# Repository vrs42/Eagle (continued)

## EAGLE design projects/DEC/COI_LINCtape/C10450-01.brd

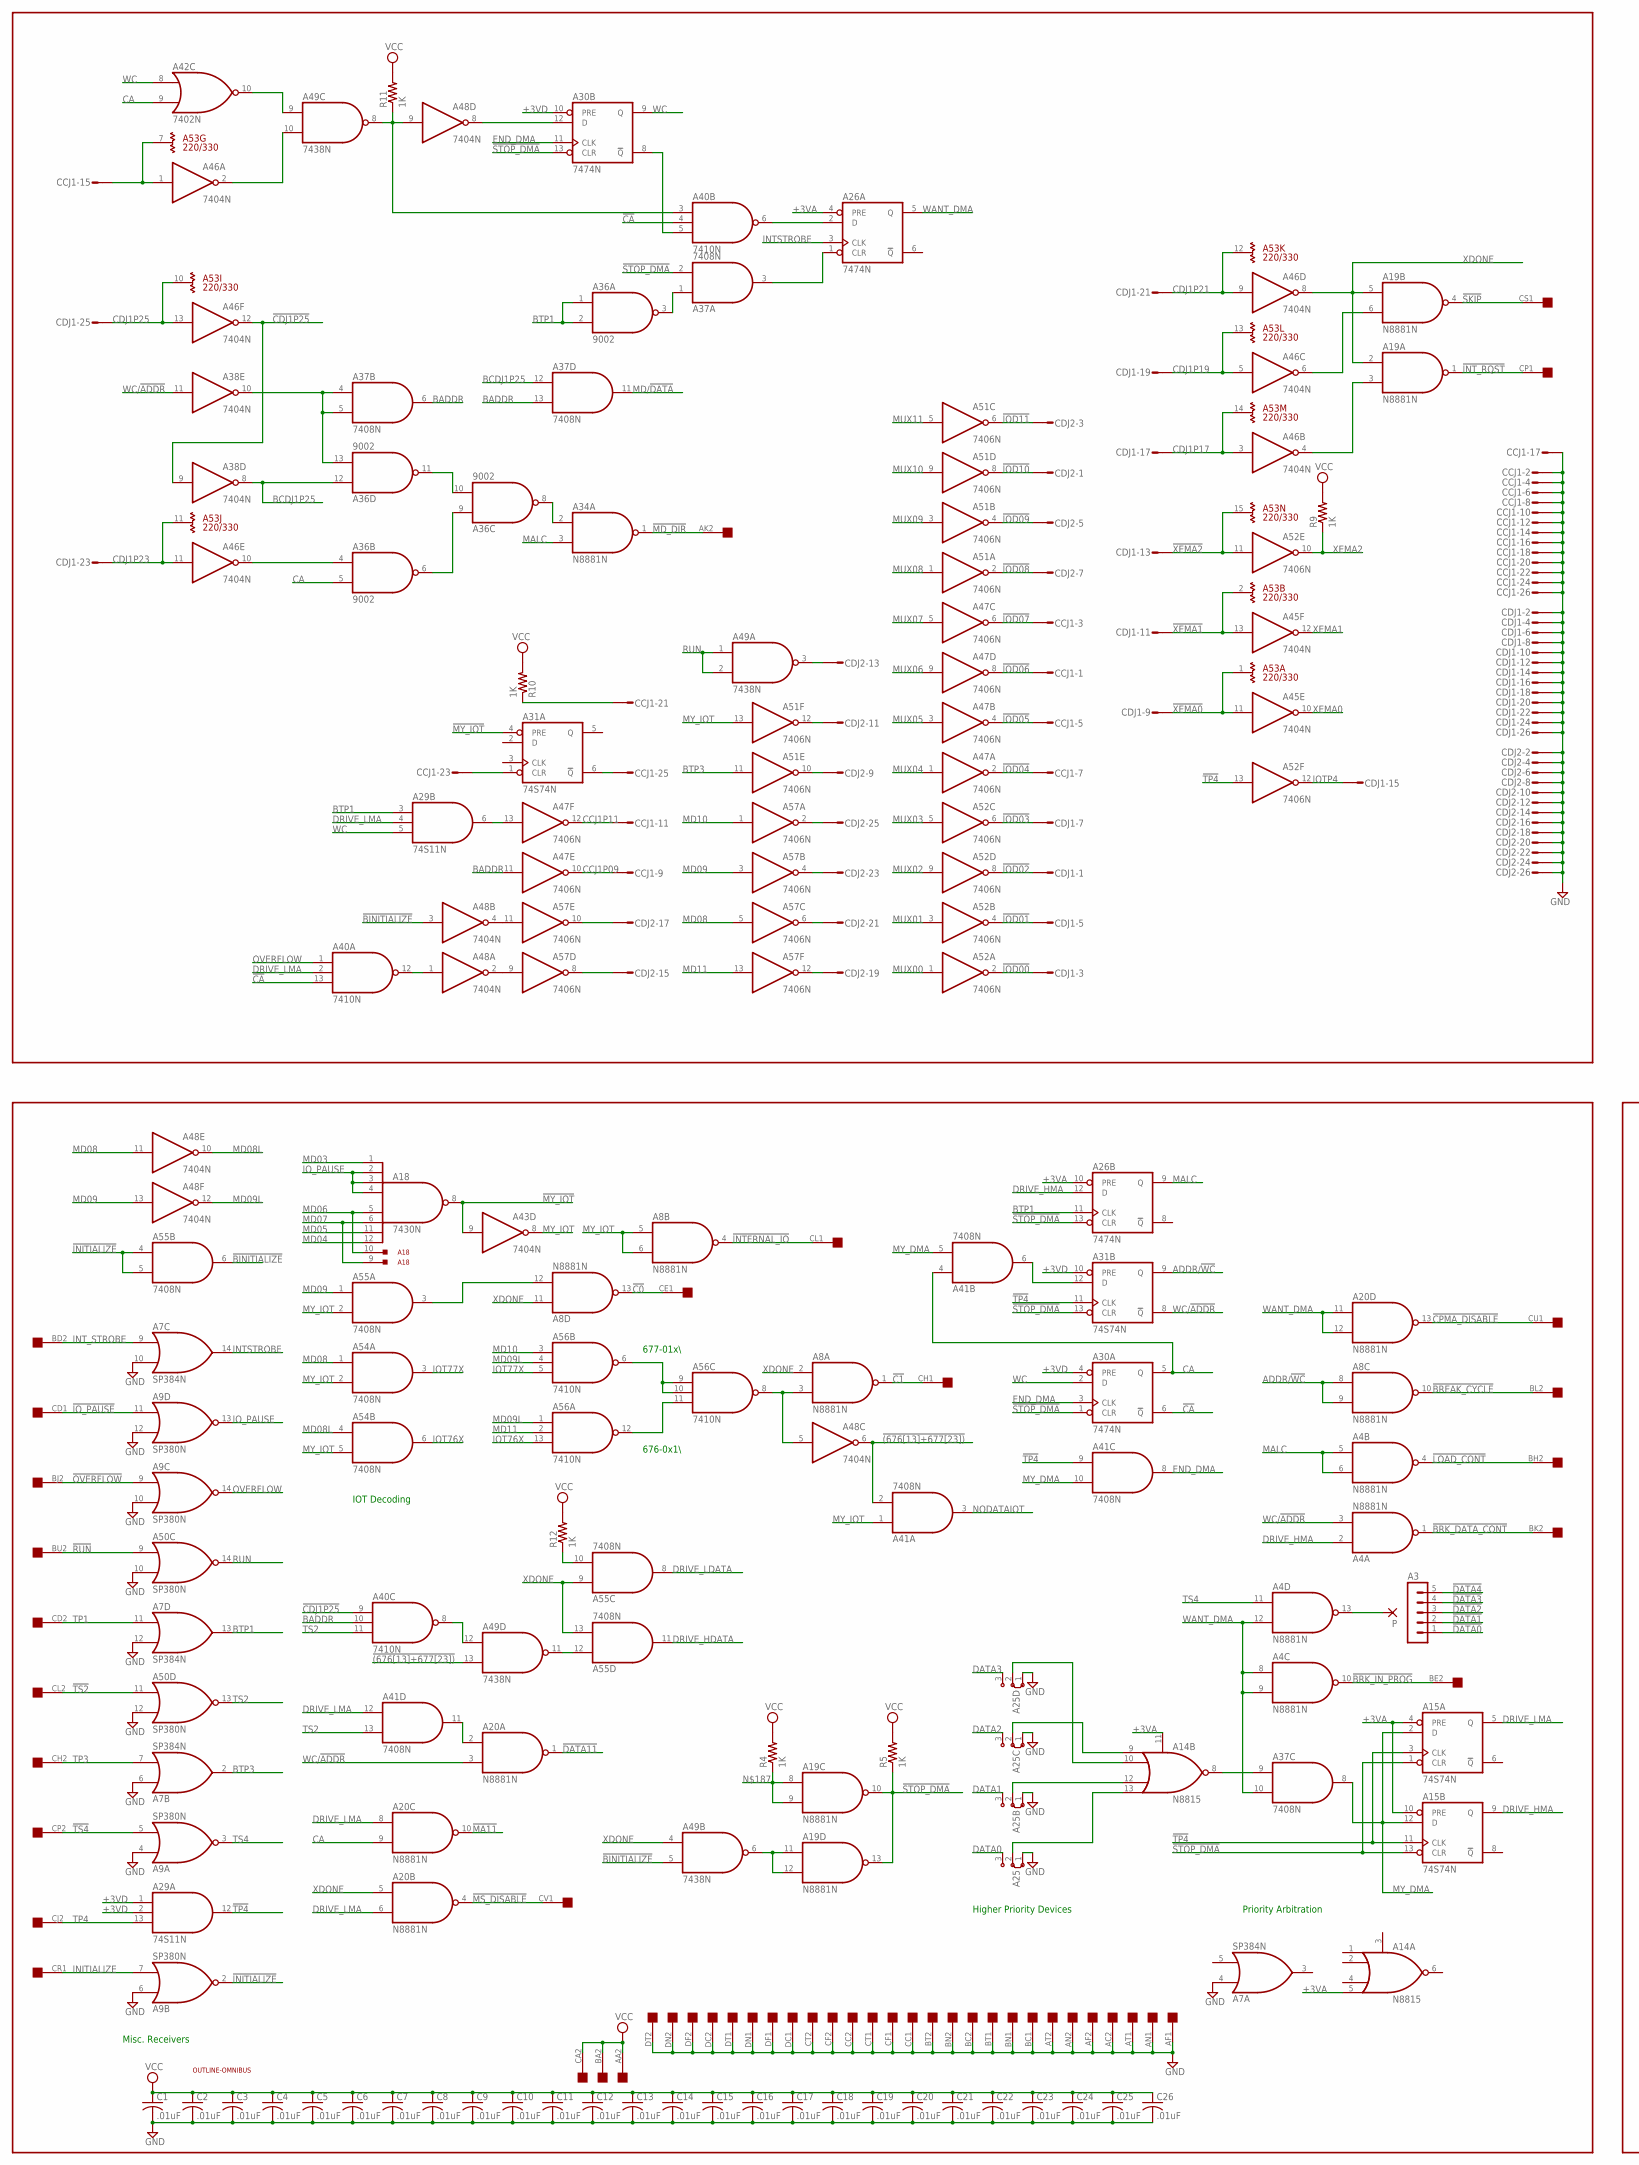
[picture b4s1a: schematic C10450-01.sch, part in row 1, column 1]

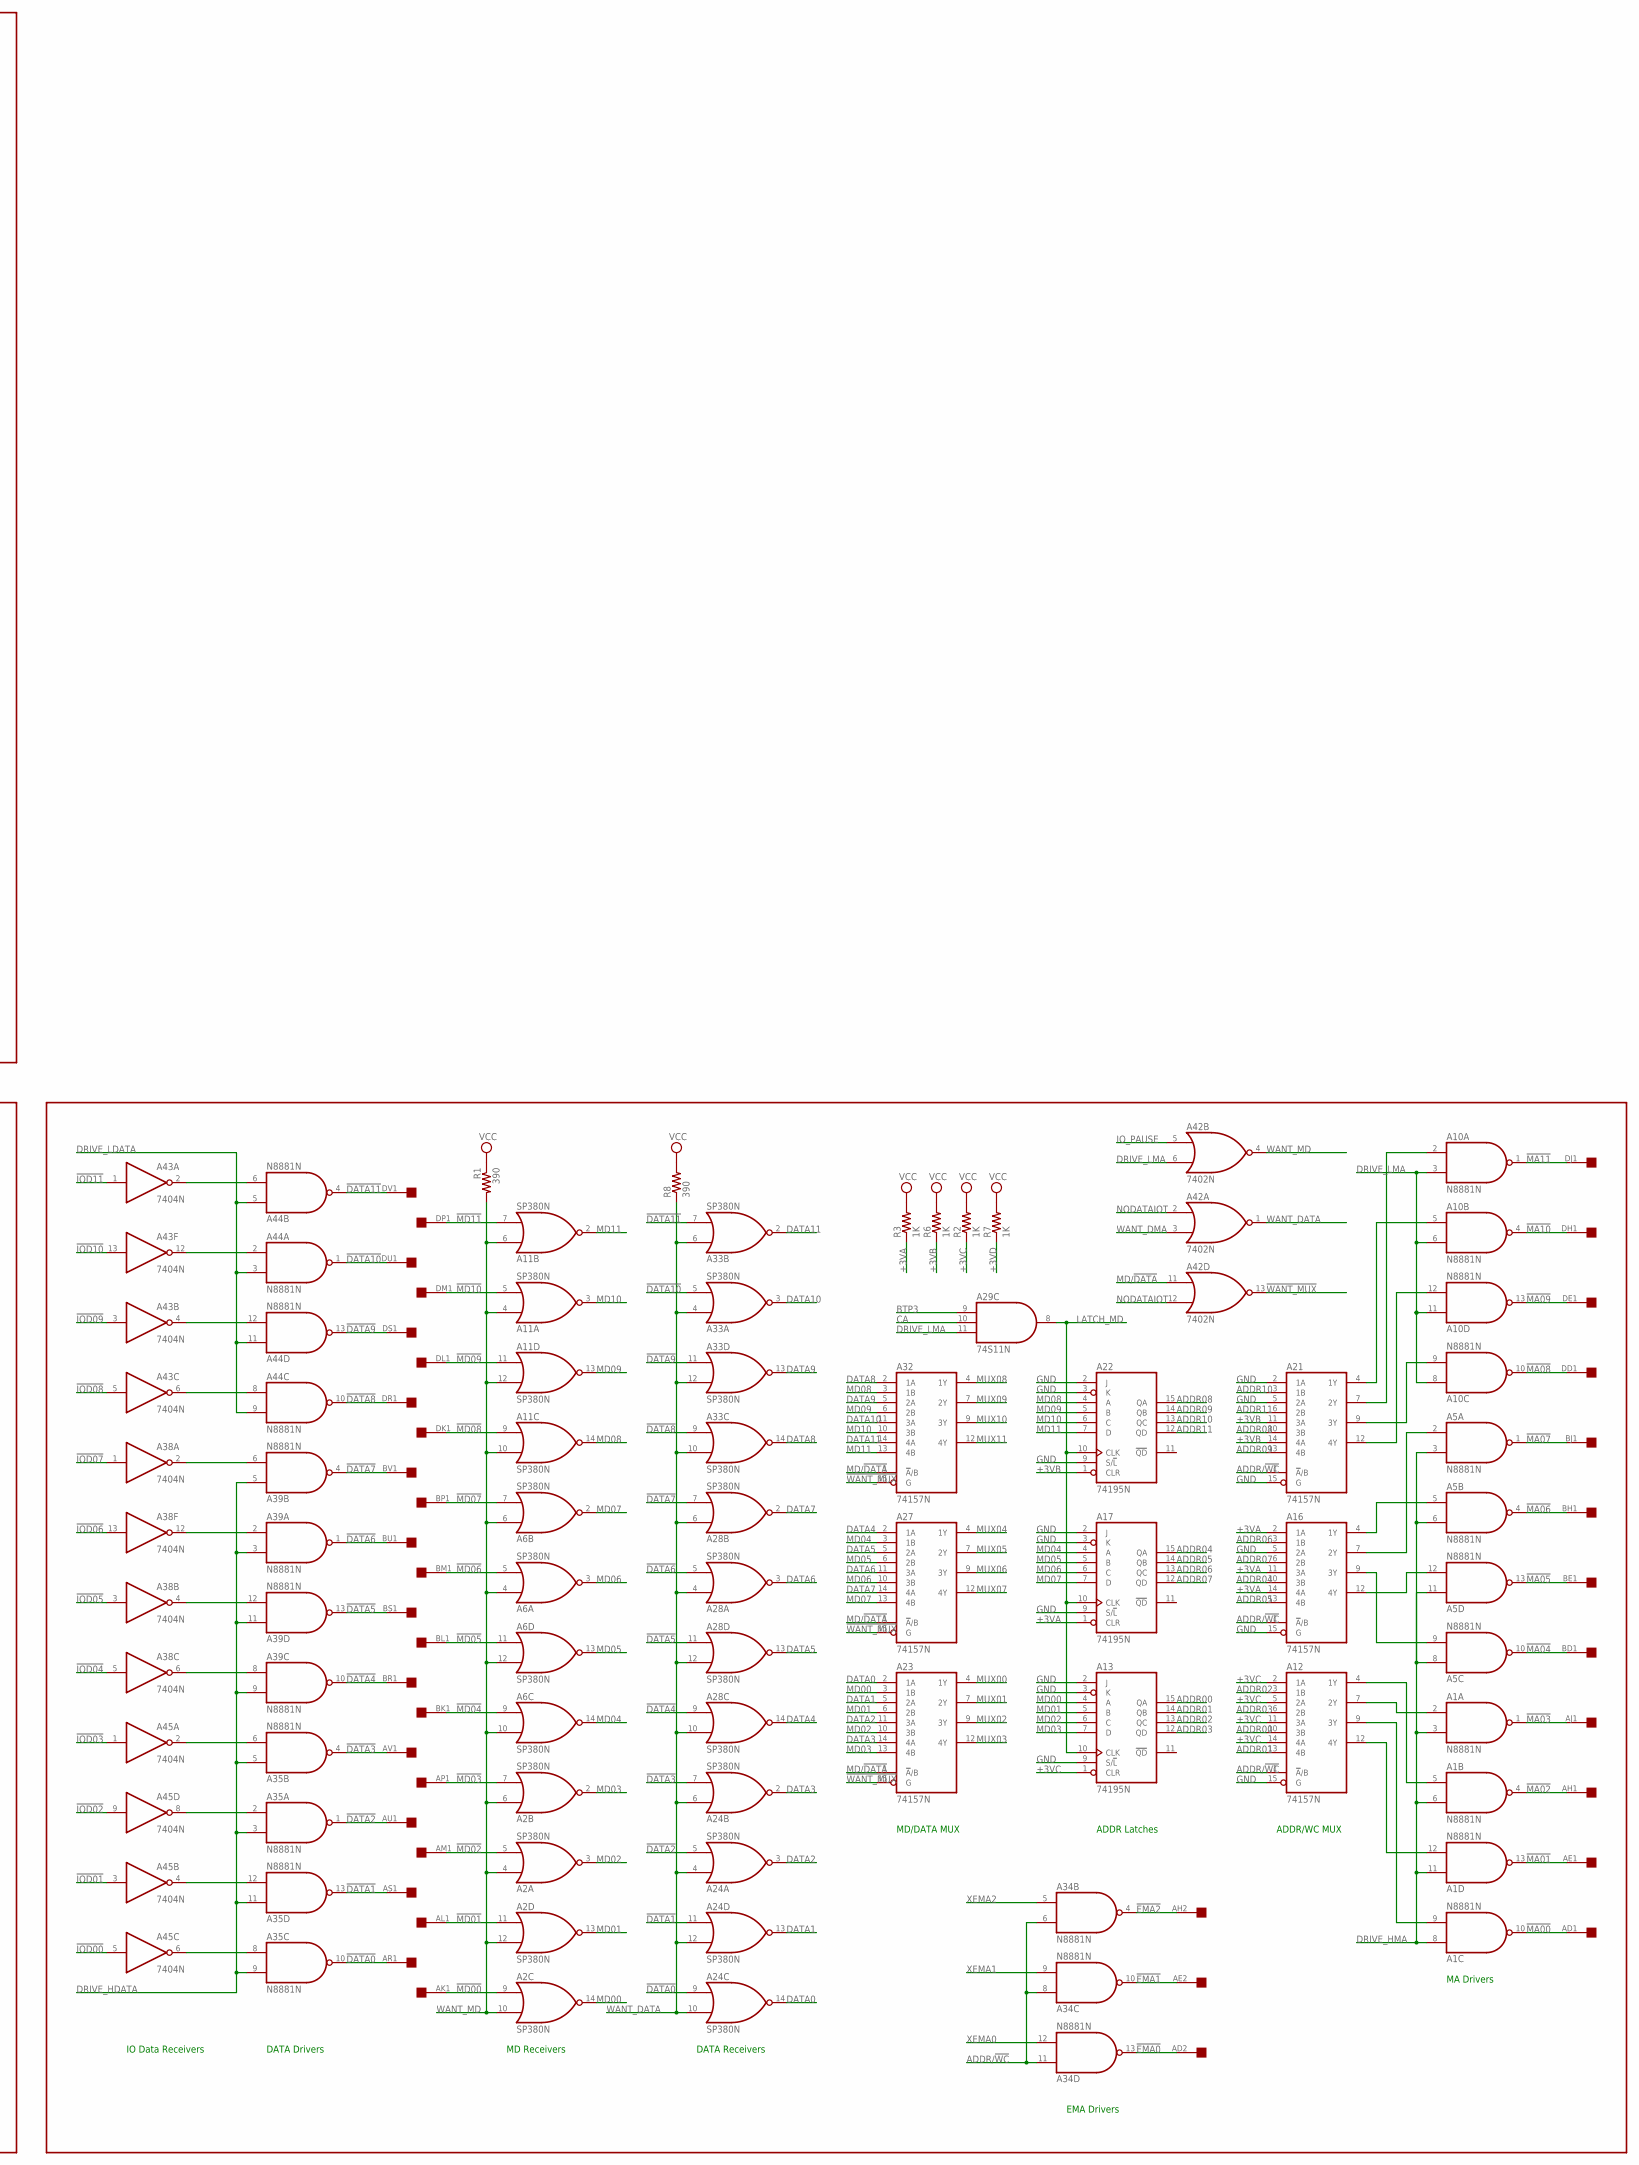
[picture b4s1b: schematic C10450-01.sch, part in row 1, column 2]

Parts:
A1, A4, A5, A8, A10, A19, A20, A34, A35, A39, A44: N8881N; DIL14
A2, A6, A9, A11, A24, A28, A33, A50: SP380N; DIL14
A3: MA05-1
A7: SP384N; DIL14
A12, A16, A21, A23, A27, A32: 74157N; DIL16
A13, A17, A22: 74195N; DIL16
A14: N8815; DIL14
A15, A31: 74S74N; DIL14
A18: 7430N; DIL14
A25, A25B, A25C, A25D: J2X5MM; 05C
A26, A30: 7474N; DIL14
A29: 74S11N; DIL14
A36: 9002; DIL14
A37, A41, A54, A55: 7408N; DIL14
A38, A43, A45, A46, A48: 7404N; DIL14
A40, A56: 7410N; DIL14
A42: 7402N; DIL14
A47, A51, A52, A57: 7406N; DIL14
A49: 7438N; DIL14
A53: 220/330; DIL16
C1, C2, C3, C4, C5, C6, C7, C8, C9, C10, C11, C12, C13, C14, C15, C16, C17, C18, C19, C20, C21, C22, C23, C24, C25, C26: .01uF; C050-025X075
CCJ1: 26HS; 26H
CDJ1, CDJ2: 26HS; 26H
P: 1,6/0,8
R1, R8: 390; 0207/10
R2, R3, R4, R5, R6, R7, R9, R10, R11, R12: 1K; 0207/10
U$1: OUTLINE-OMNIBUS; OMNIBUS
U$2: QUAD; EDGE-CON8

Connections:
!(676[13]+677[23]): A41.2 (I1), A48.6 (O), A49.13 (I1)
!BINITIALIZE: A48.3 (I), A49.5 (I1), A55.6 (O)
!BREAK_CYCLE: A8.10 (O), U$2.BL2
!BRK_DATA_CONT: A4.1 (O), U$2.BK2
!BRK_IN_PROG: A4.10 (O), U$2.BE2
!C0: A8.13 (O), U$2.CE1
!C1: A8.1 (O), U$2.CH1
!CA: A30.6 (!Q), A40.4 (I1), A40.13 (I2)
!CDJ1P25: A38.9 (I), A40.9 (I0), A46.12 (O)
!CPMA_DISABLE: A20.13 (O), U$2.CU1
!DATA0: A3.1, A24.9 (I0), A35.10 (O), U$2.AR1
!DATA1: A3.2, A24.11 (I0), A35.13 (O), U$2.AS1
!DATA2: A3.3, A24.5 (I1), A35.1 (O), U$2.AU1
!DATA3: A3.4, A24.7 (I1), A35.4 (O), U$2.AV1
!DATA4: A3.5, A28.9 (I0), A39.10 (O), U$2.BR1
!DATA5: A28.11 (I0), A39.13 (O), U$2.BS1
!DATA6: A28.5 (I1), A39.1 (O), U$2.BU1
!DATA7: A28.7 (I1), A39.4 (O), U$2.BV1
!DATA8: A33.9 (I0), A44.10 (O), U$2.DR1
!DATA9: A33.11 (I0), A44.13 (O), U$2.DS1
!DATA10: A33.5 (I1), A44.1 (O), U$2.DU1
!DATA11: A20.1 (O), A33.7 (I1), A44.4 (O), U$2.DV1
!EMA0: A34.13 (O), U$2.AD2
!EMA1: A34.10 (O), U$2.AE2
!EMA2: A34.4 (O), U$2.AH2
!INITIALIZE: A9.2 (O), A55.4 (I0), A55.5 (I1)
!INTERNAL_IO: A8.4 (O), U$2.CL1
!INT_RQST: A19.1 (O), U$2.CP1
!IOD00: A45.5 (I), A52.2 (O), CDJ1.3
!IOD01: A45.3 (I), A52.4 (O), CDJ1.5
!IOD02: A45.9 (I), A52.8 (O), CDJ1.1
!IOD03: A45.1 (I), A52.6 (O), CDJ1.7
!IOD04: A38.5 (I), A47.2 (O), CCJ1.7
!IOD05: A38.3 (I), A47.4 (O), CCJ1.5
!IOD06: A38.13 (I), A47.8 (O), CCJ1.1
!IOD07: A38.1 (I), A47.6 (O), CCJ1.3
!IOD08: A43.5 (I), A51.2 (O), CDJ2.7
!IOD09: A43.3 (I), A51.4 (O), CDJ2.5
!IOD10: A43.13 (I), A51.8 (O), CDJ2.1
!IOD11: A43.1 (I), A51.6 (O), CDJ2.3
!IO_PAUSE: A9.11 (I0), U$2.CD1
!LOAD_CONT: A4.4 (O), U$2.BH2
!MA00: A1.10 (O), U$2.AD1
!MA01: A1.13 (O), U$2.AE1
!MA02: A1.4 (O), U$2.AH1
!MA03: A1.1 (O), U$2.AJ1
!MA04: A5.10 (O), U$2.BD1
!MA05: A5.13 (O), U$2.BE1
!MA06: A5.4 (O), U$2.BH1
!MA07: A5.1 (O), U$2.BJ1
!MA08: A10.10 (O), U$2.DD1
!MA09: A10.13 (O), U$2.DE1
!MA10: A10.4 (O), U$2.DH1
!MA11: A10.1 (O), A20.10 (O), U$2.DJ1
!MD00: A2.9 (I0), U$2.AK1
!MD01: A2.11 (I0), U$2.AL1
!MD02: A2.5 (I1), U$2.AM1
!MD03: A2.7 (I1), U$2.AP1
!MD04: A6.9 (I0), U$2.BK1
!MD05: A6.11 (I0), U$2.BL1
!MD06: A6.5 (I1), U$2.BM1
!MD07: A6.7 (I1), U$2.BP1
!MD08: A11.9 (I0), U$2.DK1
!MD09: A11.11 (I0), U$2.DL1
!MD10: A11.5 (I1), U$2.DM1
!MD11: A11.7 (I1), U$2.DP1
!MD_DIR: A34.1 (O), U$2.AK2
!MS_DISABLE: A20.4 (O), U$2.CV1
!MY_IOT: A18.8 (O), A31.4 (PRE), A43.9 (I)
!OVERFLOW: A9.9 (I0), U$2.BJ2
!RUN: A50.9 (I0), U$2.BU2
!SKIP: A19.4 (O), U$2.CS1
!STOP_DMA: A15.1 (CLR), A15.13 (CLR), A19.10 (O), A19.13 (O), A26.13 (CLR), A30.1 (CLR), A30.13 (CLR), A31.13 (CLR), A37.2 (I1), R5.1
!TP4: A15.3 (CLK), A15.11 (CLK), A29.12 (O), A31.11 (CLK), A41.9 (I0), A52.13 (I)
!TS2: A50.11 (I0), U$2.CL2
!TS4: A9.5 (I1), U$2.CP2
!WANT_MUX: A23.15 (G), A27.15 (G), A32.15 (G), A42.13 (O)
!WC: A30.8 (!Q), A40.5 (I2)
!XEMA0: A45.11 (I), A53.1 (TERM), CDJ1.9
!XEMA1: A45.13 (I), A53.2 (TERM), CDJ1.11
!XEMA2: A52.11 (I), A53.15 (TERM), CDJ1.13
+3VA: A14.5 (I3), A14.11 (G), A15.4 (PRE), A15.10 (PRE), A16.2 (1A), A16.11 (3A), A16.14 (4A), A17.1 (CLR), A26.4 (PRE), A26.10 (PRE), R3.1
+3VB: A21.11 (3A), A21.14 (4A), A22.1 (CLR), R6.1
+3VC: A12.2 (1A), A12.5 (2A), A12.11 (3A), A12.14 (4A), A13.1 (CLR), R2.1
+3VD: A29.1 (I0), A29.2 (I1), A30.4 (PRE), A30.10 (PRE), A31.10 (PRE), R7.1
ADDR00: A12.10 (3B), A13.15 (QA)
ADDR01: A12.13 (4B), A13.14 (QB)
ADDR02: A12.3 (1B), A13.13 (QC)
ADDR03: A12.6 (2B), A13.12 (QD)
ADDR04: A16.10 (3B), A17.15 (QA)
ADDR05: A16.13 (4B), A17.14 (QB)
ADDR06: A16.3 (1B), A17.13 (QC)
ADDR07: A16.6 (2B), A17.12 (QD)
ADDR08: A21.10 (3B), A22.15 (QA)
ADDR09: A21.13 (4B), A22.14 (QB)
ADDR10: A21.3 (1B), A22.13 (QC)
ADDR11: A21.6 (2B), A22.12 (QD)
ADDR/!WC: A8.8 (I0), A8.9 (I1), A12.1 (!A!/B), A16.1 (!A!/B), A21.1 (!A!/B), A31.9 (Q), A34.6 (I1), A34.8 (I0), A34.11 (I0)
BADDR: A37.6 (O), A37.13 (I1), A40.10 (I1), A47.11 (I)
BCDJ1P25: A36.12 (I0), A37.12 (I0), A38.8 (O)
BTP1: A7.13 (O), A26.11 (CLK), A29.3 (I0), A36.1 (I0), A36.2 (I1)
BTP3: A7.2 (O), A29.9 (I0), A51.11 (I)
CA: A20.9 (I1), A29.10 (I1), A30.5 (Q), A36.5 (I1), A41.4 (I0), A42.9 (I1)
CCJ1P09: A47.10 (O), CCJ1.9
CCJ1P11: A47.12 (O), CCJ1.11
CDJ1P17: A46.3 (I), A53.14 (TERM), CDJ1.17
CDJ1P19: A46.5 (I), A53.13 (TERM), CDJ1.19
CDJ1P21: A46.9 (I), A53.12 (TERM), CDJ1.21
CDJ1P23: A46.11 (I), A53.11 (TERM), CDJ1.23
CDJ1P25: A46.13 (I), A53.10 (TERM), CDJ1.25
CDJ2P09: A51.10 (O), CDJ2.9
CDJ2P11: A51.12 (O), CDJ2.11
CDJ2P13: A49.3 (O), CDJ2.13
CDJ2P15: A57.8 (O), CDJ2.15
CDJ2P17: A57.10 (O), CDJ2.17
CDJ2P19: A57.12 (O), CDJ2.19
CDJ2P21: A57.6 (O), CDJ2.21
CDJ2P23: A57.4 (O), CDJ2.23
CDJ2P25: A57.2 (O), CDJ2.25
DATA0: A23.2 (1A), A24.14 (O), A25.3
DATA1: A23.5 (2A), A24.13 (O), A25B.3
DATA2: A23.11 (3A), A24.3 (O), A25C.3
DATA3: A23.14 (4A), A24.2 (O), A25D.3
DATA4: A27.2 (1A), A28.14 (O)
DATA5: A27.5 (2A), A28.13 (O)
DATA6: A27.11 (3A), A28.3 (O)
DATA7: A27.14 (4A), A28.2 (O)
DATA8: A32.2 (1A), A33.14 (O)
DATA9: A32.5 (2A), A33.13 (O)
DATA10: A32.11 (3A), A33.3 (O)
DATA11: A32.14 (4A), A33.2 (O)
DRIVE_HDATA: A35.3 (I1), A35.5 (I0), A35.9 (I1), A35.11 (I0), A39.3 (I1), A39.5 (I0), A39.9 (I1), A39.11 (I0), A55.11 (O)
DRIVE_HMA: A1.3 (I1), A1.6 (I1), A1.8 (I0), A1.11 (I0), A4.2 (I0), A5.3 (I1), A5.6 (I1), A5.8 (I0), A5.11 (I0), A15.9 (Q), A26.12 (D)
DRIVE_LDATA: A44.3 (I1), A44.5 (I0), A44.9 (I1), A44.11 (I0), A55.8 (O)
DRIVE_LMA: A10.3 (I1), A10.6 (I1), A10.8 (I0), A10.11 (I0), A15.5 (Q), A20.6 (I1), A20.8 (I0), A29.4 (I1), A29.11 (I2), A40.2 (I1), A41.12 (I0), A42.6 (I1)
END_DMA: A30.3 (CLK), A30.11 (CLK), A41.8 (O)
GND: A1.7 (GND), A2.1 (GND), A4.7 (GND), A5.7 (GND), A6.1 (GND), A7.1 (GND), A7.4 (I0), A7.6 (I0), A7.10 (I1), A7.12 (I1), A8.7 (GND), A9.1 (GND), A9.4 (I0), A9.6 (I0), A9.10 (I1), A9.12 (I1), A10.7 (GND), A11.1 (GND), A12.8 (GND), A12.15 (G), A13.2 (J), A13.3 (K), A13.8 (GND), A13.9 (S/!L), A14.7 (GND), A15.7 (GND), A16.5 (2A), A16.8 (GND), A16.15 (G), A17.2 (J), A17.3 (K), A17.8 (GND), A17.9 (S/!L), A18.7 (GND), A19.7 (GND), A20.7 (GND), A21.2 (1A), A21.5 (2A), A21.8 (GND), A21.15 (G), A22.2 (J), A22.3 (K), A22.8 (GND), A22.9 (S/!L), A23.8 (GND), A24.1 (GND), A25.1, A25B.1, A25C.1, A25D.1, A26.7 (GND), A27.8 (GND), A28.1 (GND), A29.7 (GND), A30.7 (GND), A31.7 (GND), A32.8 (GND), A33.1 (GND), A34.7 (GND), A35.7 (GND), A36.7 (GND), A37.7 (GND), A38.7 (GND), A39.7 (GND), A40.7 (GND), A41.7 (GND), A42.7 (GND), A43.7 (GND), A44.7 (GND), A45.7 (GND), A46.7 (GND), A47.7 (GND), A48.7 (GND), A49.7 (GND), A50.1 (GND), A50.10 (I1), A50.12 (I1), A51.7 (GND), A52.7 (GND), A53.8 (GND), A54.7 (GND), A55.7 (GND), A56.7 (GND), A57.7 (GND), C1.2, C2.2, C3.2, C4.2, C5.2, C6.2, C7.2, C8.2, C9.2, C10.2, C11.2, C12.2, C13.2, C14.2, C15.2, C16.2, C17.2, C18.2, C19.2, C20.2, C21.2, C22.2, C23.2, C24.2, C25.2, C26.2, CCJ1.2, CCJ1.4, CCJ1.6, CCJ1.8, CCJ1.10, CCJ1.12, CCJ1.14, CCJ1.16, CCJ1.17, CCJ1.18, CCJ1.20, CCJ1.22, CCJ1.24, CCJ1.26, CDJ1.2, CDJ1.4, CDJ1.6, CDJ1.8, CDJ1.10, CDJ1.12, CDJ1.14, CDJ1.16, CDJ1.18, CDJ1.20, CDJ1.22, CDJ1.24, CDJ1.26, CDJ2.2, CDJ2.4, CDJ2.6, CDJ2.8, CDJ2.10, CDJ2.12, CDJ2.14, CDJ2.16, CDJ2.18, CDJ2.20, CDJ2.22, CDJ2.24, CDJ2.26, U$2.AC2, U$2.AF1, U$2.AF2, U$2.AN1, U$2.AN2, U$2.AT1, U$2.AT2, U$2.BC1, U$2.BC2, U$2.BN1, U$2.BN2, U$2.BT1, U$2.BT2, U$2.CC1, U$2.CC2, U$2.CF1, U$2.CF2, U$2.CT1, U$2.CT2, U$2.DC1, U$2.DC2, U$2.DF1, U$2.DF2, U$2.DN1, U$2.DN2, U$2.DT1, U$2.DT2
INITIALIZE: A9.7 (I1), U$2.CR1
INTSTROBE: A7.14 (O), A26.3 (CLK)
INT_STROBE: A7.9 (I0), U$2.BD2
IOT76X: A54.6 (O), A56.13 (I2)
IOT77X: A54.3 (O), A56.5 (I2)
IOTP4: A52.12 (O), CDJ1.15
IO_PAUSE: A9.13 (O), A18.2 (I1), A18.3 (I2), A18.4 (I3), A42.5 (I0)
LATCH_MD: A13.10 (CLK), A17.10 (CLK), A22.10 (CLK), A29.8 (O)
MALC: A4.5 (I0), A4.6 (I1), A26.9 (Q), A34.3 (I1)
MD00: A2.14 (O), A13.4 (A), A23.3 (1B)
MD01: A2.13 (O), A13.5 (B), A23.6 (2B)
MD02: A2.3 (O), A13.6 (C), A23.10 (3B)
MD03: A2.2 (O), A13.7 (D), A18.1 (I0), A23.13 (4B)
MD04: A6.14 (O), A17.4 (A), A18.12 (I7), A27.3 (1B)
MD05: A6.13 (O), A17.5 (B), A18.11 (I6), A27.6 (2B)
MD06: A6.3 (O), A17.6 (C), A18.5 (I4), A18.10, A27.10 (3B)
MD07: A6.2 (O), A17.7 (D), A18.6 (I5), A18.9, A27.13 (4B)
MD08: A11.14 (O), A22.4 (A), A32.3 (1B), A48.11 (I), A54.1 (I0), A57.5 (I)
MD08L: A48.10 (O), A54.4 (I0)
MD09: A11.13 (O), A22.5 (B), A32.6 (2B), A48.13 (I), A55.1 (I0), A57.3 (I)
MD09L: A48.12 (O), A56.1 (I0), A56.4 (I1)
MD10: A11.3 (O), A22.6 (C), A32.10 (3B), A56.3 (I0), A57.1 (I)
MD11: A11.2 (O), A22.7 (D), A32.13 (4B), A56.2 (I1), A57.13 (I)
MD/!DATA: A23.1 (!A!/B), A27.1 (!A!/B), A32.1 (!A!/B), A37.11 (O), A42.11 (I0)
MUX00: A23.4 (1Y), A52.1 (I)
MUX01: A23.7 (2Y), A52.3 (I)
MUX02: A23.9 (3Y), A52.9 (I)
MUX03: A23.12 (4Y), A52.5 (I)
MUX04: A27.4 (1Y), A47.1 (I)
MUX05: A27.7 (2Y), A47.3 (I)
MUX06: A27.9 (3Y), A47.9 (I)
MUX07: A27.12 (4Y), A47.5 (I)
MUX08: A32.4 (1Y), A51.1 (I)
MUX09: A32.7 (2Y), A51.3 (I)
MUX10: A32.9 (3Y), A51.9 (I)
MUX11: A32.12 (4Y), A51.5 (I)
MY_DMA: A15.2 (D), A15.12 (D), A37.8 (O), A41.5 (I1), A41.10 (I1)
MY_IOT: A8.5 (I0), A8.6 (I1), A41.1 (I0), A43.8 (O), A51.13 (I), A54.2 (I1), A54.5 (I1), A55.2 (I1)
unnamed: A1.9 (I1), A12.9 (3Y)
unnamed: A1.12 (I1), A12.12 (4Y)
unnamed: A36.6 (O), A36.9 (I0)
unnamed: A1.5 (I0), A12.4 (1Y)
unnamed: A56.6 (O), A56.9 (I0), A56.10 (I1)
unnamed: A1.2 (I0), A12.7 (2Y)
unnamed: A8.3 (I1), A48.5 (I), A56.8 (O)
unnamed: A14.10 (I1), A25D.2
unnamed: A36.4 (I0), A46.10 (O)
unnamed: A42.10 (O), A49.9 (I0)
unnamed: A10.5 (I0), A21.4 (1Y)
unnamed: A10.2 (I0), A21.7 (2Y)
unnamed: A14.8 (O), A37.9 (I0)
unnamed: A31.1 (CLR), CCJ1.23
unnamed: A4.13 (O), P.1
unnamed: A26.1 (CLR), A37.3 (O)
unnamed: A26.2 (D), A40.6 (O)
unnamed: A5.12 (I1), A16.12 (4Y)
unnamed: A5.9 (I1), A16.9 (3Y)
unnamed: A5.2 (I0), A16.7 (2Y)
unnamed: A46.2 (O), A49.10 (I1)
unnamed: A49.11 (O), A55.12 (I0)
unnamed: A29.6 (O), A47.13 (I)
unnamed: A8.12 (I1), A55.3 (O)
unnamed: A40.12 (O), A48.1 (I)
unnamed: A10.12 (I1), A21.12 (4Y)
unnamed: A10.9 (I1), A21.9 (3Y)
unnamed: A5.5 (I0), A16.4 (1Y)
unnamed: A31.6 (!Q), CCJ1.25
unnamed: CCJ1.21, R10.1
unnamed: A46.1 (I), A53.7 (TERM), CCJ1.15
unnamed: A19.8 (I0), A19.9 (I1), R4.1
unnamed: A40.3 (I0), A48.9 (I), A49.8 (O), R11.1
unnamed: A19.3 (I1), A46.4 (O)
unnamed: A19.11 (I0), A19.12 (I1), A49.6 (O)
unnamed: A14.13 (I3), A25.2
unnamed: A14.9 (I0), A25C.2
unnamed: A14.12 (I2), A25B.2
unnamed: A43.2 (O), A44.6 (I1)
unnamed: A48.2 (O), A57.9 (I)
unnamed: A31.12 (D), A41.6 (O)
unnamed: A40.8 (O), A49.12 (I0)
unnamed: A30.12 (D), A48.8 (O)
unnamed: A38.2 (O), A39.6 (I1)
unnamed: A19.6 (I1), A46.6 (O)
unnamed: A20.2 (I0), A41.11 (O)
unnamed: A34.2 (I0), A36.8 (O)
unnamed: A35.12 (I1), A45.4 (O)
unnamed: A35.8 (I0), A45.6 (O)
unnamed: A35.6 (I1), A45.2 (O)
unnamed: A35.2 (I0), A45.8 (O)
unnamed: A36.13 (I1), A37.4 (I0), A37.5 (I1), A38.10 (O)
unnamed: A36.10 (I1), A36.11 (O)
unnamed: A36.3 (O), A37.1 (I0)
unnamed: A38.6 (O), A39.8 (I0)
unnamed: A38.4 (O), A39.12 (I1)
unnamed: A38.12 (O), A39.2 (I0)
unnamed: A43.6 (O), A44.8 (I0)
unnamed: A43.4 (O), A44.12 (I1)
unnamed: A43.12 (O), A44.2 (I0)
unnamed: A55.10 (I1), R12.1
unnamed: A48.4 (O), A57.11 (I)
unnamed: A56.11 (I2), A56.12 (O)
NODATAIOT: A41.3 (O), A42.2 (I0), A42.12 (I1)
OVERFLOW: A9.14 (O), A40.1 (I0)
RUN: A49.1 (I0), A49.2 (I1), A50.14 (O)
TP1: A7.11 (I0), U$2.CD2
TP3: A7.7 (I1), U$2.CH2
TP4: A29.13 (I2), U$2.CJ2
TS2: A40.11 (I2), A41.13 (I1), A50.13 (O)
TS4: A4.11 (I0), A9.3 (O)
VCC: A1.14 (VCC), A2.8 (VCC), A4.14 (VCC), A5.14 (VCC), A6.8 (VCC), A7.8 (VCC), A8.14 (VCC), A9.8 (VCC), A10.14 (VCC), A11.8 (VCC), A12.16 (VCC), A13.16 (VCC), A14.14 (VCC), A15.14 (VCC), A16.16 (VCC), A17.16 (VCC), A18.14 (VCC), A19.14 (VCC), A20.14 (VCC), A21.16 (VCC), A22.16 (VCC), A23.16 (VCC), A24.8 (VCC), A26.14 (VCC), A27.16 (VCC), A28.8 (VCC), A29.14 (VCC), A30.14 (VCC), A31.14 (VCC), A32.16 (VCC), A33.8 (VCC), A34.14 (VCC), A35.14 (VCC), A36.14 (VCC), A37.14 (VCC), A38.14 (VCC), A39.14 (VCC), A40.14 (VCC), A41.14 (VCC), A42.14 (VCC), A43.14 (VCC), A44.14 (VCC), A45.14 (VCC), A46.14 (VCC), A47.14 (VCC), A48.14 (VCC), A49.14 (VCC), A50.8 (VCC), A51.14 (VCC), A52.14 (VCC), A53.16 (VCC), A54.14 (VCC), A55.14 (VCC), A56.14 (VCC), A57.14 (VCC), C1.1, C2.1, C3.1, C4.1, C5.1, C6.1, C7.1, C8.1, C9.1, C10.1, C11.1, C12.1, C13.1, C14.1, C15.1, C16.1, C17.1, C18.1, C19.1, C20.1, C21.1, C22.1, C23.1, C24.1, C25.1, C26.1, R1.1, R2.2, R3.2, R4.2, R5.2, R6.2, R7.2, R8.2, R9.2, R10.2, R11.2, R12.2, U$2.AA2, U$2.BA2, U$2.CA2
WANT_DATA: A24.4 (I0), A24.6 (I0), A24.10 (I1), A24.12 (I1), A28.4 (I0), A28.6 (I0), A28.10 (I1), A28.12 (I1), A33.4 (I0), A33.6 (I0), A33.10 (I1), A33.12 (I1), A42.1 (O), R8.1
WANT_DMA: A4.8 (I0), A4.9 (I1), A4.12 (I1), A20.11 (I0), A20.12 (I1), A26.5 (Q), A37.10 (I1), A42.3 (I1)
WANT_MD: A2.4 (I0), A2.6 (I0), A2.10 (I1), A2.12 (I1), A6.4 (I0), A6.6 (I0), A6.10 (I1), A6.12 (I1), A11.4 (I0), A11.6 (I0), A11.10 (I1), A11.12 (I1), A42.4 (O), R1.2
WC: A29.5 (I2), A30.2 (D), A30.9 (Q), A42.8 (I0)
WC/!ADDR: A4.3 (I1), A20.3 (I1), A31.8 (!Q), A38.11 (I)
XDONE: A8.2 (I0), A8.11 (I0), A19.2 (I0), A19.5 (I0), A20.5 (I0), A46.8 (O), A49.4 (I0), A55.9 (I0), A55.13 (I1)
XEMA0: A34.12 (I1), A45.10 (O)
XEMA1: A34.9 (I1), A45.12 (O)
XEMA2: A34.5 (I0), A52.10 (O), R9.1

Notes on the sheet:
MD Receivers
DATA Receivers
MD/DATA MUX
ADDR Latches
ADDR/WC MUX
MA Drivers
EMA Drivers
DATA Drivers
IO Data Receivers
Higher Priority Devices
Priority Arbitration
Misc. Receivers
IOT Decoding
677-01x\\
676-0x1\\

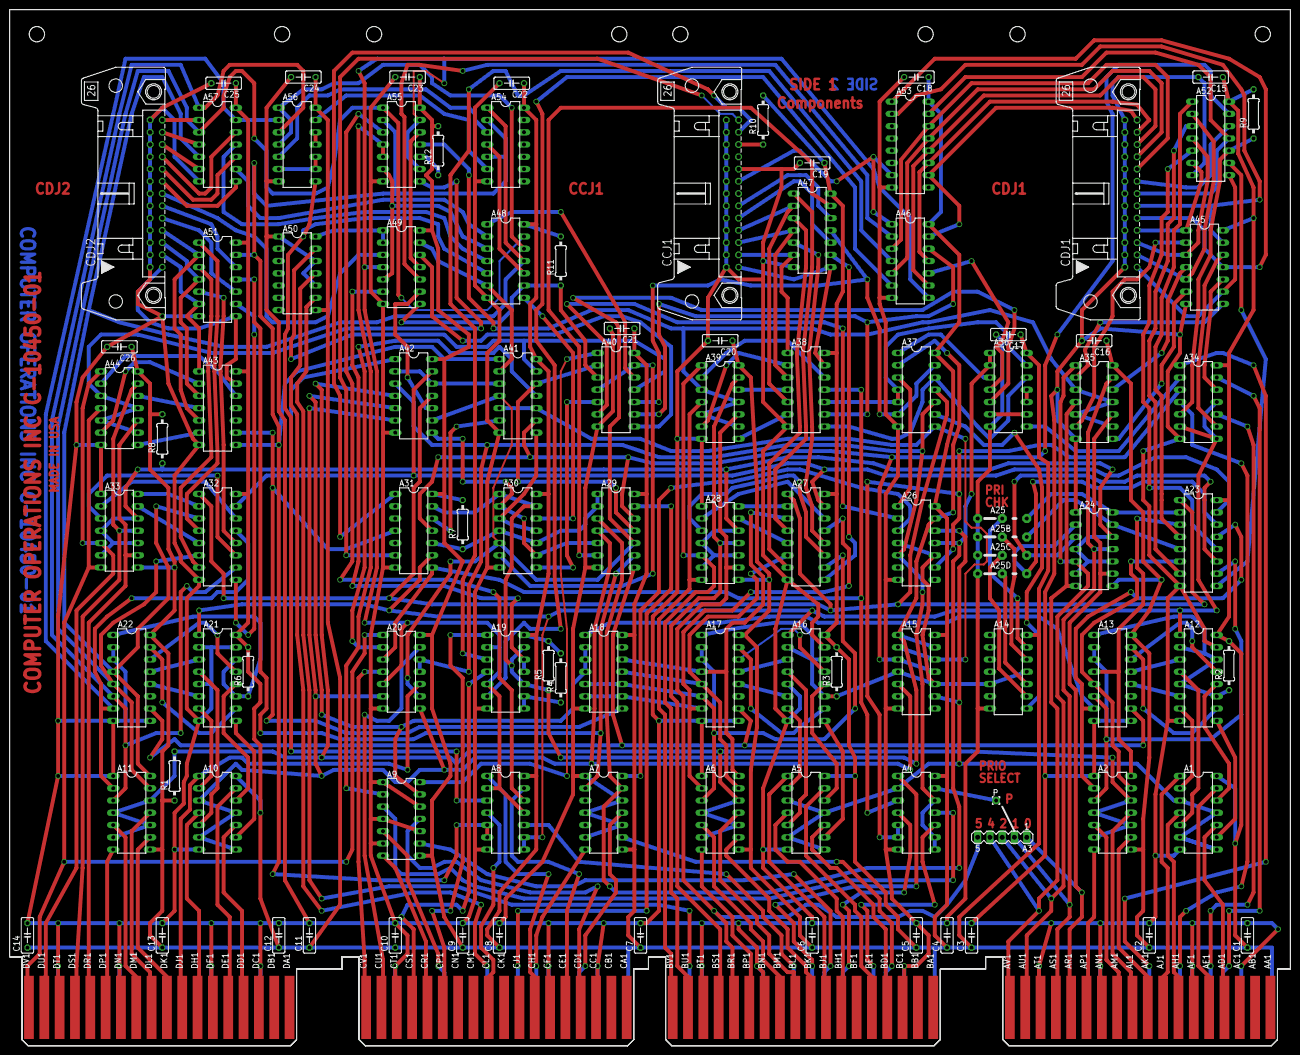
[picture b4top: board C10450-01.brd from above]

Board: 3 copper layers, 265.3 x 214.6 mm, 104 parts (0 on the bottom side), 256 nets.
